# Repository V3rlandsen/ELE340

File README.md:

# ELE340 Gruppe D
ELE340 Gruppe D prosjekt

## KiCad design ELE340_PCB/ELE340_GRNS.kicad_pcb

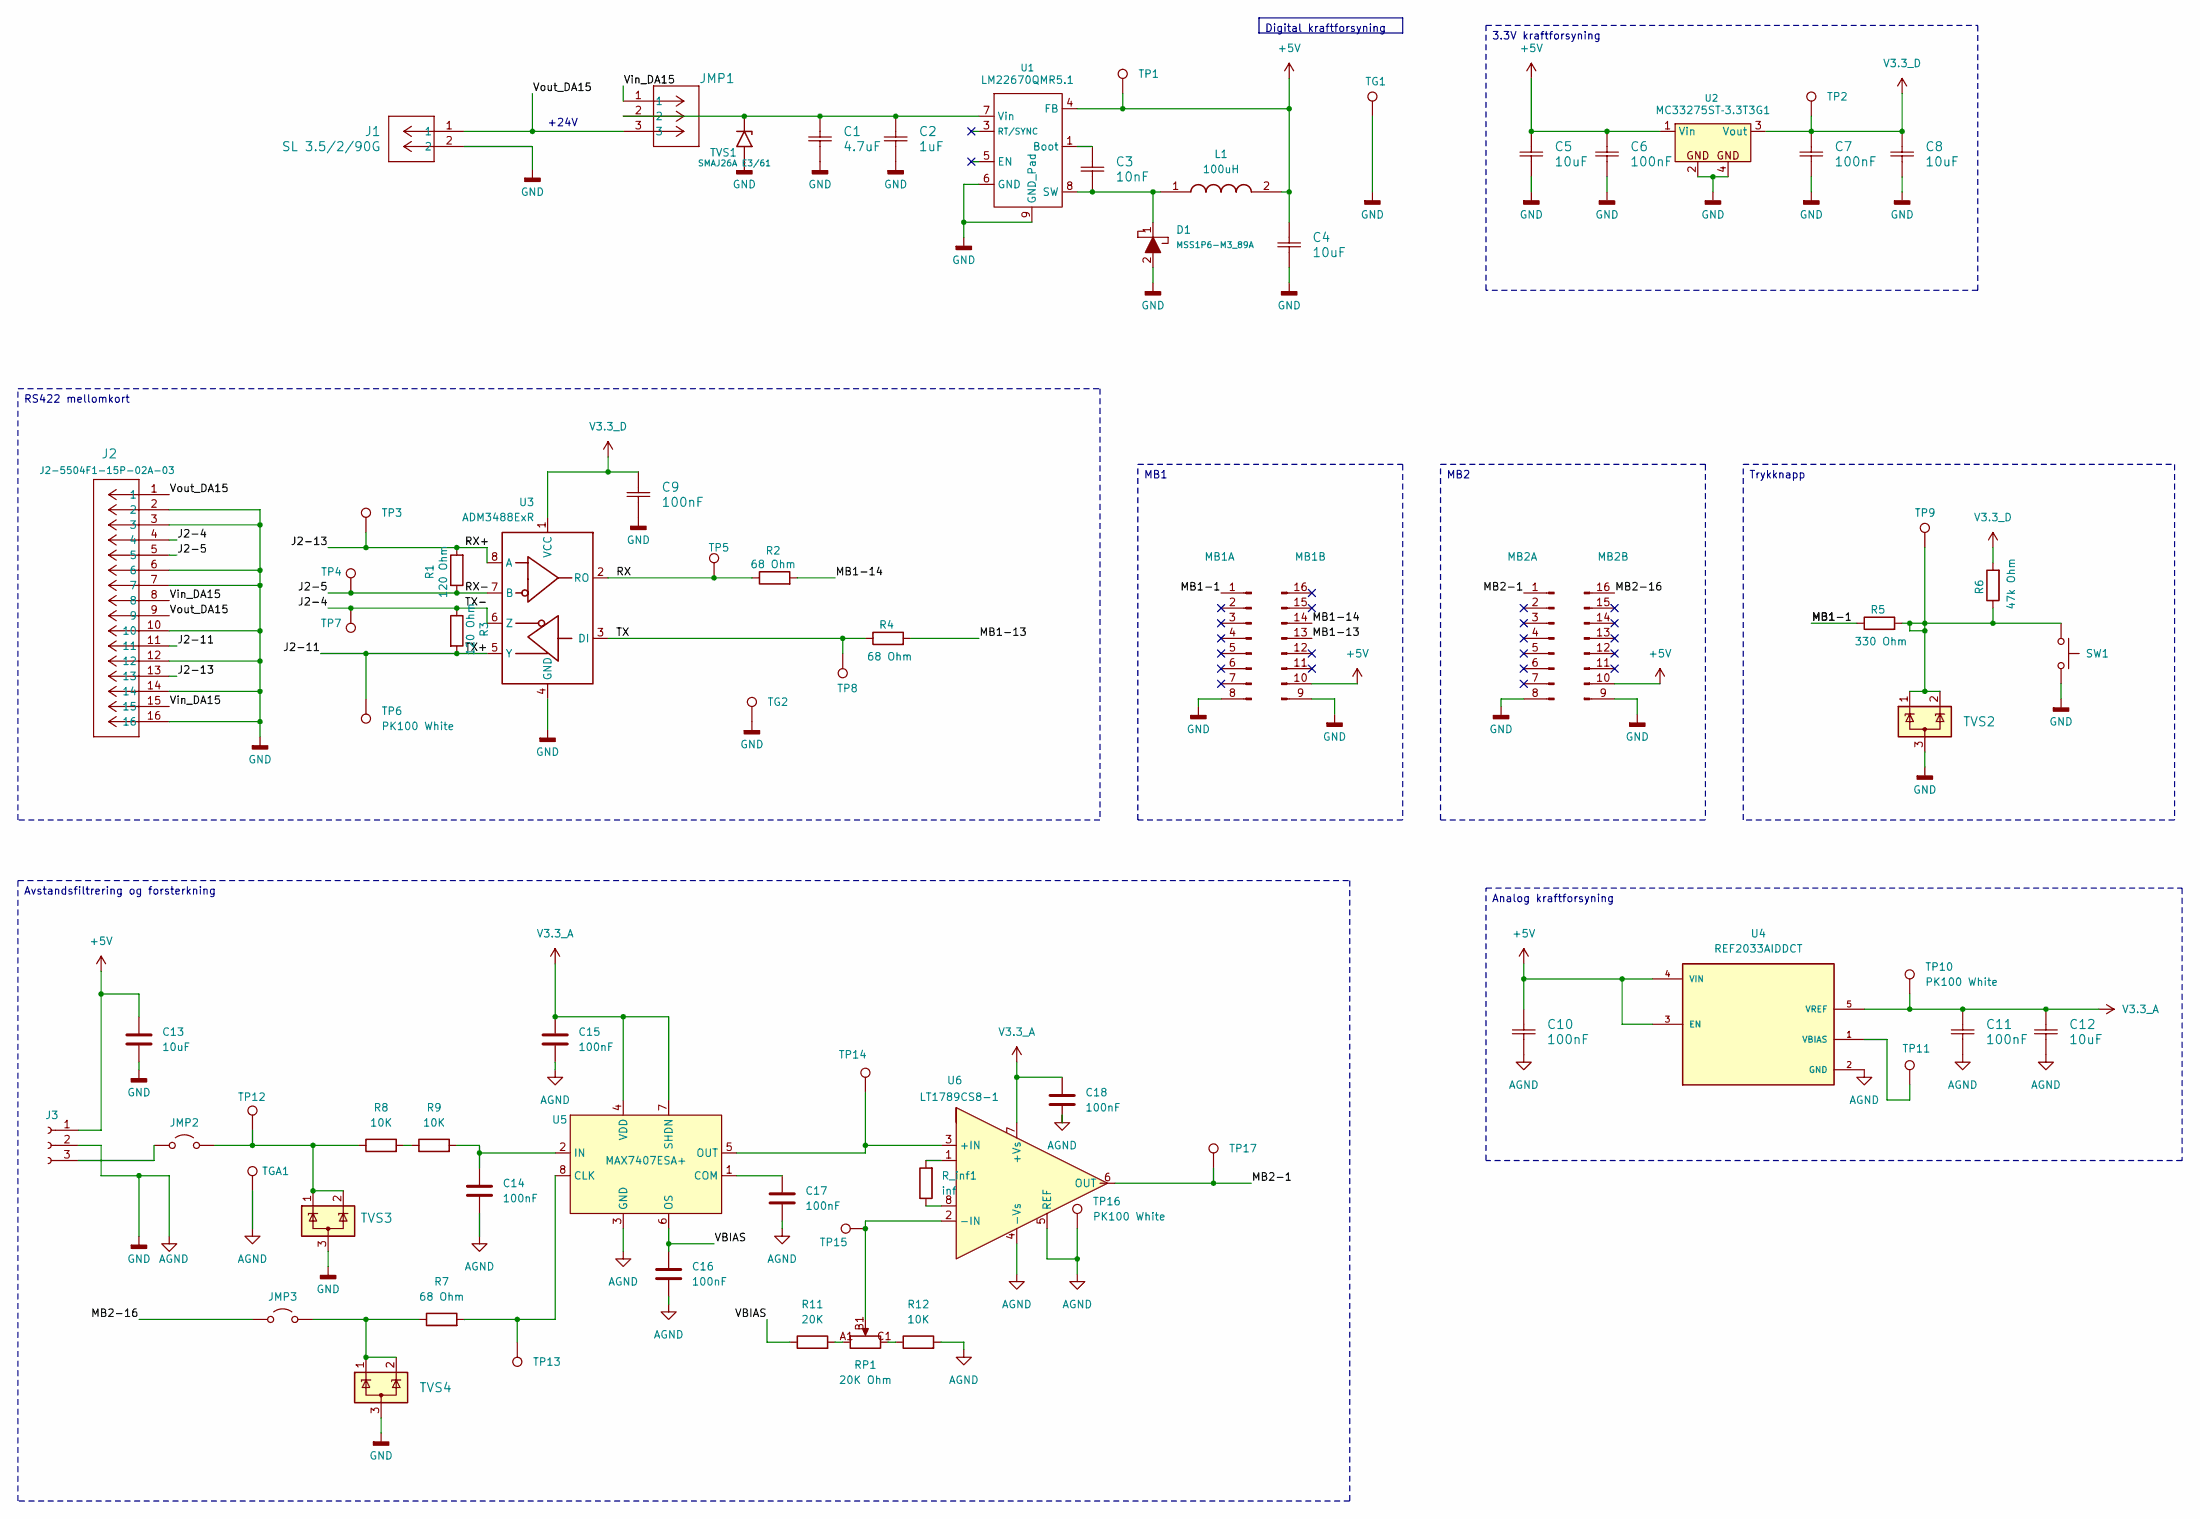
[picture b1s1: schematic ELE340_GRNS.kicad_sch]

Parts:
C1: 4.7uF; C_1206_3216Metric_Pad1.33x1.80mm_HandSolder
C2: 1uF; C_1206_3216Metric_Pad1.33x1.80mm_HandSolder
C3: 10nF; C_1206_3216Metric_Pad1.33x1.80mm_HandSolder
C4, C5, C8, C12, C13: 10uF; C_1210_3225Metric_Pad1.33x2.70mm_HandSolder
C6, C7, C9, C10, C11, C14, C15, C16, C17, C18: 100nF; C_1206_3216Metric_Pad1.33x1.80mm_HandSolder
D1: MSS1P6-M3_89A; D_MicroSMP_AK; Manufacturer_Part_Number MSS1P6-M3/89A
J1: SL 3.5/2/90G; SL3.5-2-90G
J2: J2-5504F1-15P-02A-03; D-SUB 15P MALE RA
J3: Conn_01x03_Socket; SL3.5-3-90G
JMP1: PinHeader_1x03_P2.54mm_Vertical
JMP2, JMP3: Jumper_2_Open; JMP2-3
L1: 100uH; SDR2207101KL; Manufacturer_Part_Number SDR2207-101KL
MB1, MB2: Conn_01x08_Pin; MB_2.54mm
R1, R3: 120 Ohm; R_1206_3216Metric_Pad1.30x1.75mm_HandSolder
R2, R4, R7: 68 Ohm; R_1206_3216Metric_Pad1.30x1.75mm_HandSolder
R5: 330 Ohm; R_1206_3216Metric_Pad1.30x1.75mm_HandSolder
R6: 47k Ohm; R_1206_3216Metric_Pad1.30x1.75mm_HandSolder
R8, R9, R12: 10K; R_1206_3216Metric_Pad1.30x1.75mm_HandSolder
R11: 20K; R_1206_3216Metric_Pad1.30x1.75mm_HandSolder
RP1: 20K Ohm; RP1
R_inf1: inf; R_1206_3216Metric_Pad1.30x1.75mm_HandSolder
SW1: 430182070816
TG1, TG2: PK100 White; TP; Manufacturer_Part_Number 20-313143
TGA1: PK100 White; TP
TP1, TP2, TP3, TP4, TP5, TP6, TP7, TP8, TP9, TP10, TP11, TP12, TP13, TP14, TP15, TP16, TP17: PK100 White; TP; Manufacturer_Part_Number 20-313143
TVS1: SMAJ26A E3/61; D_SMA_Handsoldering
TVS2, TVS3, TVS4: TVS -PESD3V3U1UT_215; SOT-23_Handsoldering
U1: LM22670QMR5.1; SOIC-8-1EP_3.9x4.9mm_P1.27mm_EP2.95x4.9mm_Mask2.71x3.4mm
U2: MC33275ST‐3.3T3G1; SOT-223
U3: ADM3488ExR; SOIC-8_3.9x4.9mm_P1.27mm
U4: REF2033AIDDCT; SOT-23-5_HandSoldering; PARTREV D
U5: MAX7407ESA+; SOIC-8_3.9x4.9mm_P1.27mm
U6: LT1789CS8-1; SOIC-8_3.9x4.9mm_P1.27mm

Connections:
+5V: C4.1, C5.1, C6.1, C10.1, C13.1, J3.1, L1.2, MB1.10, MB2.10, TP1.1, U1.4 (FB), U2.1 (Vin), U4.3 (EN), U4.4 (VIN)
/J2-4: J2.4, R3.1, TP7.1, U3.6 (Z)
/J2-5: J2.5, R1.1, TP4.1, U3.7 (B)
/J2-11: J2.11, R3.2, TP6.1, U3.5 (Y)
/J2-13: J2.13, R1.2, TP3.1, U3.0.9 (A), U3.8 (A)
/MB1: MB1.1, R5.1
/MB1-13: MB1.13, R4.2
/MB1-14: MB1.14, R2.2
/MB2-1: MB2.1, TP17.1, U6.6 (OUT)
/MB2-16: JMP3.1 (A), MB2.16
/RX: R2.1, TP5.1, U3.2 (RO)
/TX: R4.1, TP8.1, U3.3 (DI)
/VBIAS: C16.1, R11.1, U5.6 (OS)
/Vin_DA15: J2.8, J2.15, JMP1.1
/Vout_DA15: J1.1, J2.1, J2.9, JMP1.3
AGND: C1.2, C2.2, C4.2, C5.2, C6.2, C7.2, C8.2, C9.2, C10.2, C11.2, C12.2, C13.2, C14.2, C15.2, C16.2, C17.2, C18.2, D1.2, J1.2, J2.2, J2.3, J2.6, J2.7, J2.10, J2.12, J2.14, J2.16, J3.2, MB1.8, MB1.9, MB2.8, MB2.9, R12.2, SW1.3 (B), SW1.4 (B), TG1.1, TG2.1, TGA1.1, TP16.1, TVS1.2 (A2), TVS2.3 (A), TVS3.3 (A), TVS4.3 (A), U1.6 (GND), U1.9 (GND_Pad), U2.2, U2.4, U3.4 (GND), U4.2 (GND), U5.3 (GND), U6.4 (-Vs), U6.5 (REF)
unnamed: J3.3, JMP2.1 (A)
unnamed: JMP2.2 (B), R8.1, TP12.1, TVS3.1 (K), TVS3.2 (K)
unnamed: JMP3.2 (B), R7.1, TVS4.1 (K), TVS4.2 (K)
unnamed: R5.2, R6.1, SW1.1 (A), SW1.2 (A), TP9.1, TVS2.1 (K), TVS2.2 (K)
unnamed: R8.2, R9.1
unnamed: R11.2, RP1.A1
unnamed: R12.1, RP1.C1
unnamed: R_inf1.1, U6.8
unnamed: R_inf1.2, U6.1
unnamed: C1.1, C2.1, JMP1.2, TVS1.1 (A1), U1.7 (Vin)
unnamed: C3.1, U1.1 (Boot)
unnamed: C3.2, D1.1, L1.1, U1.8 (SW)
unnamed: TP11.1, U4.1 (VBIAS)
unnamed: R7.2, TP13.1, U5.8 (CLK)
unnamed: C17.1, U5.1 (COM)
unnamed: C14.1, R9.2, U5.2 (IN)
unnamed: TP14.1, U5.5 (OUT), U6.3 (+IN)
unnamed: RP1.B1, TP15.1, U6.2 (-IN)
V3.3_A: C11.1, C12.1, C15.1, C18.1, TP10.1, U4.5 (VREF), U5.4 (VDD), U5.7 (SHDN), U6.7 (+Vs)
V3.3_D: C7.1, C8.1, C9.1, R6.2, TP2.1, U2.3 (Vout), U3.1 (VCC)

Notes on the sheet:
+24V
RS422 mellomkort
Trykknapp
Digital kraftforsyning
Avstandsfiltrering og forsterkning
Analog kraftforsyning
MB1
MB2
3.3V kraftforsyning

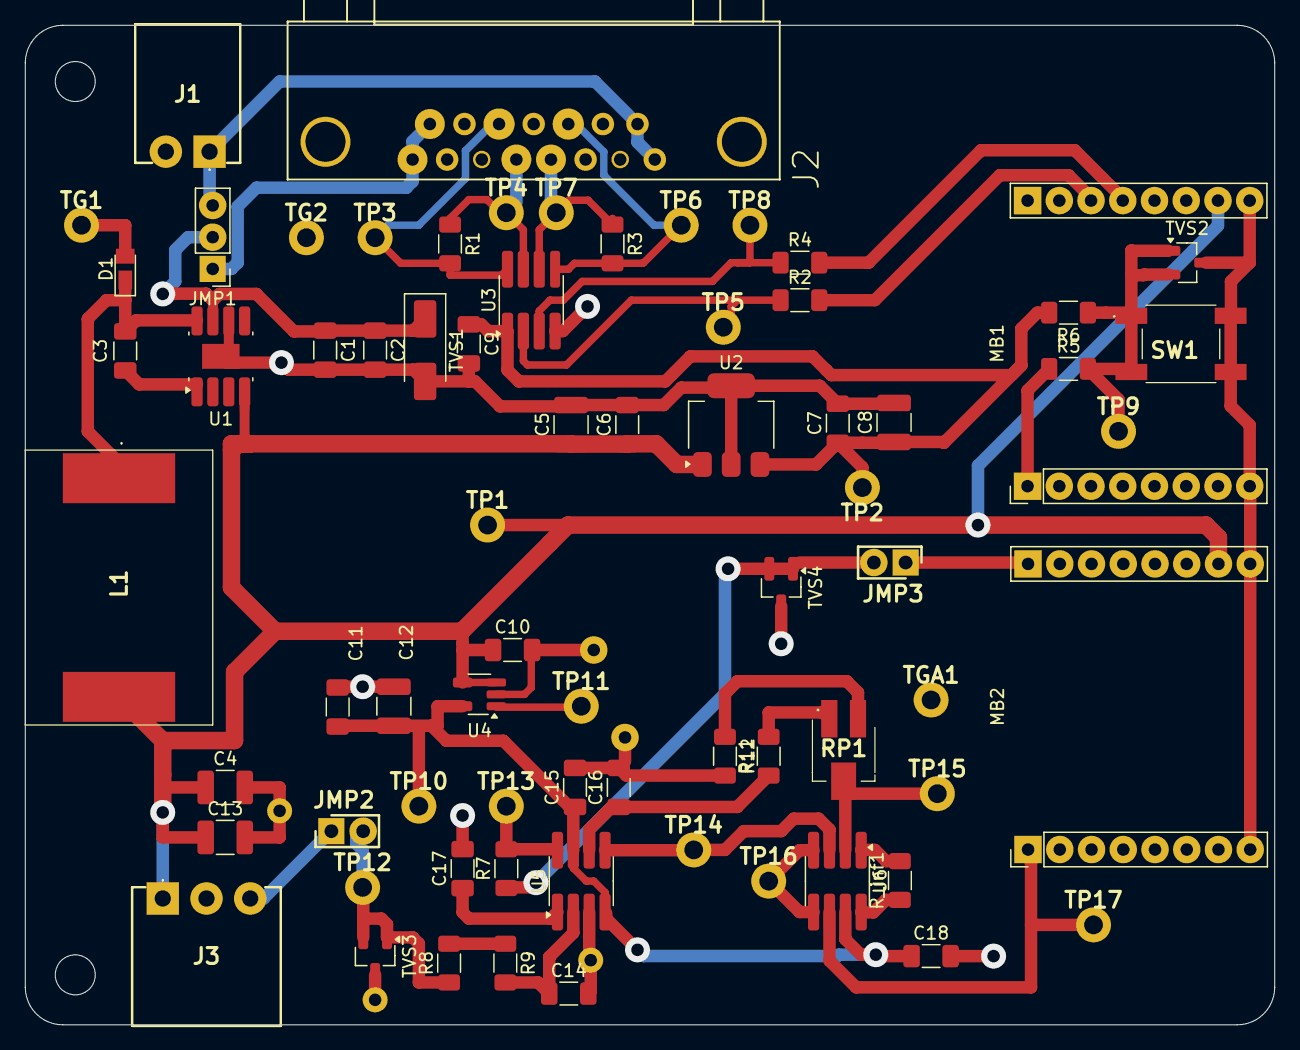
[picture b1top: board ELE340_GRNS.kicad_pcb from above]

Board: 2 copper layers, 100.0 x 80.0 mm, 72 parts (0 on the bottom side), 36 nets.
